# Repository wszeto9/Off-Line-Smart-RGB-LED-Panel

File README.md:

# Off-Line Smart RGB LED Panel
A constant current driver made to to drive 100W RGB COB LEDs straight from mains power

[Interactive BOM](https://htmlpreview.github.io/?https://github.com/wszeto9/Off-Line-Smart-RGBCCT-LED-Panel/blob/main/ibom.html)

## Testing and Validation

This is probably the most complicated board I've made so far! This isn't because it has more circuits or anything, but rather because it's powered off AC mains. I can't just plug it in and hope that it works. There's an insignificant chance it doesn't, and who knows what will happen to the circuit if a component doesn't work as expected. It goes without saying, don't try this at home! It's taken me years to feel okay designing a system like this, and it isn't a project to build on a whim. Nevertheless, let's look into the bringup process. 

### 24VDC Buck

One of the easiest things to test is the 24V Buck converter. Solder it up, and stick +50VDC (0.1A max) between +HV and -HV. It's safe enough for me to feel comfortable testing it alone. Flip the power switch, and the conviniently placed LED indicator turns on, suggesting that the power rail works. Sticking a multimeter on the power rail shows... ***25.5V***? Interesting. I wonder if it's because there's no load on it. I'll have to look at it again once I get some load put together. For now, it's fine. The 3.3V regulator doesn't care as long as it's below 28V, and the LED drivers are okay with up to a few hundred volts. The LNK3206 IC the design is based on also has a soft-start feature, and that seems to work great. Rise time seems to be ~ 16 ms, no overshoots or anything. Cool! 

*Soft-start of 24V rail. +HV = 60V DC*

### Bulk Capacitor Discharge Testing

Before I even consider plugging this into the wall, I need to ensure that the bulk capacitors are able to drain in a reasonable time after being unplugged. Bulk capacitors without bleed resistors are one of the scariest things to see. There's no telling whether it's at 400V or 0V simply by looking, and one slip up during measurement would be very dangerous. In this test, I'll inject +60VDC between +HV and -HV. Then I'll measure the voltage across C2. +60VDC is high enough that I can extrapolate discharge rate to +169VDC, while also being low enough that I'd be okay starting with it. 

*Schematic of Bleed Circuit, Rev A02*

*Voltage across C2 after +HV is turned off. Initial discharge rate seems to be approximately 20V/100ms, or 200V/s*

Looking at the discharge rate, it seems to be much higher than expected. The calculations show a 15 second time-constant from a 1M/15.5uF system. The measured time constant is much less than 1 second. This might be since the Buck converter is attached to the circuit, which has ~ 10k of load at 24V. Assuming 100% efficiency, that would equate to ~ 24k of load at 60V, and it's also a psudo-constant power load since the buck converter wants to keep the output at 24V. With a 24k / 15.5uF system, that gets a tau of 0.36 seconds, fairly close to what's observed. The constant power load also explain why the discharge rate seems to accelerate when the capacitor voltage gets closer to 25V.

### LED Current Regulation Testing, 62VDC

Once the +24V Buck was validated, the LED driver can be validated next. +HV is set to +62VDC since that's the highest 2x 30V power supplies can deliver. A 12V LED strip was used to be a load for testing. The LED strip drew 1A at 12V for a total of 12W of power draw. The power supplies were set to 0.2A max in order to ensure that in the event that the LED driver did not work, the LEDs would not be supplied past their rated power. 

When powered up, the LEDs do not turn on until a 3.3V PWM signal was applied. Once the PWM signal was applied, the LED strip did not shine at full brightness. This is likely because the LD configuration only allows for full power draw when +HV is at 169VDC. Since +HV is +62VDC, the LEDs are likely at roughly 1/3 the maximum current draw. 

Scope capture of LED current regulation, Rev A02. +HV = 62V, PWM = 20% Duty Cycle, 3.3V logic. Blue = PWM, Green = GATE, Yellow = Isense. 0.1V on Isense is 0.33A.

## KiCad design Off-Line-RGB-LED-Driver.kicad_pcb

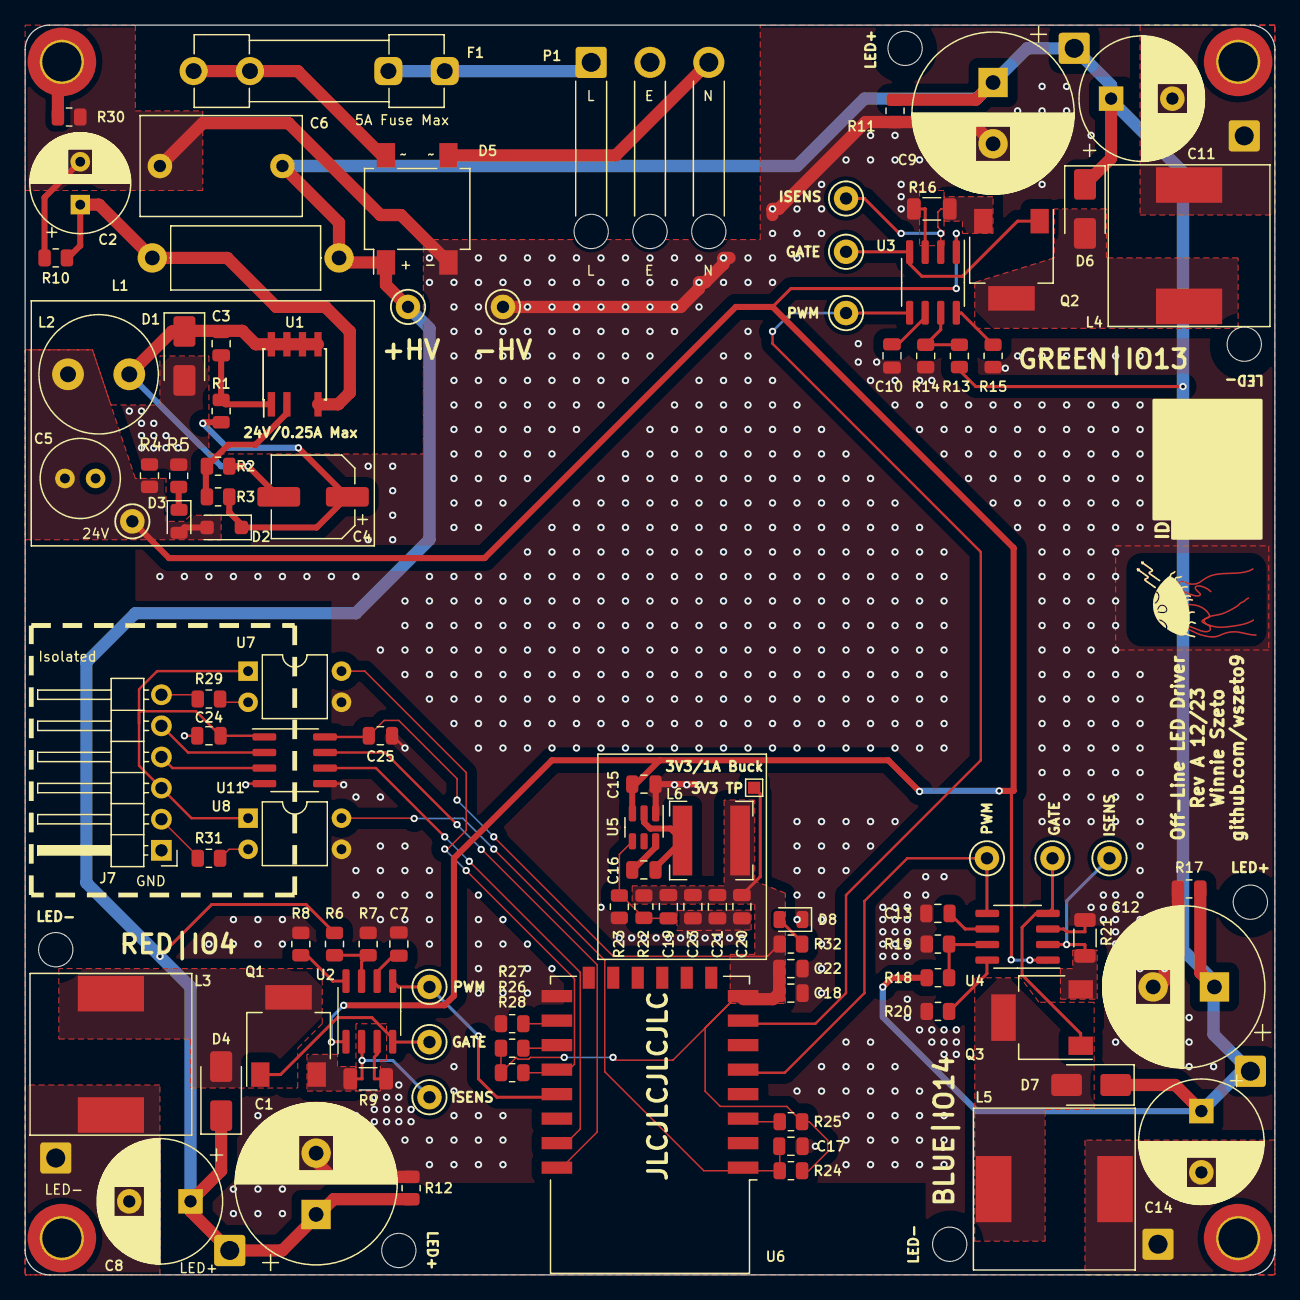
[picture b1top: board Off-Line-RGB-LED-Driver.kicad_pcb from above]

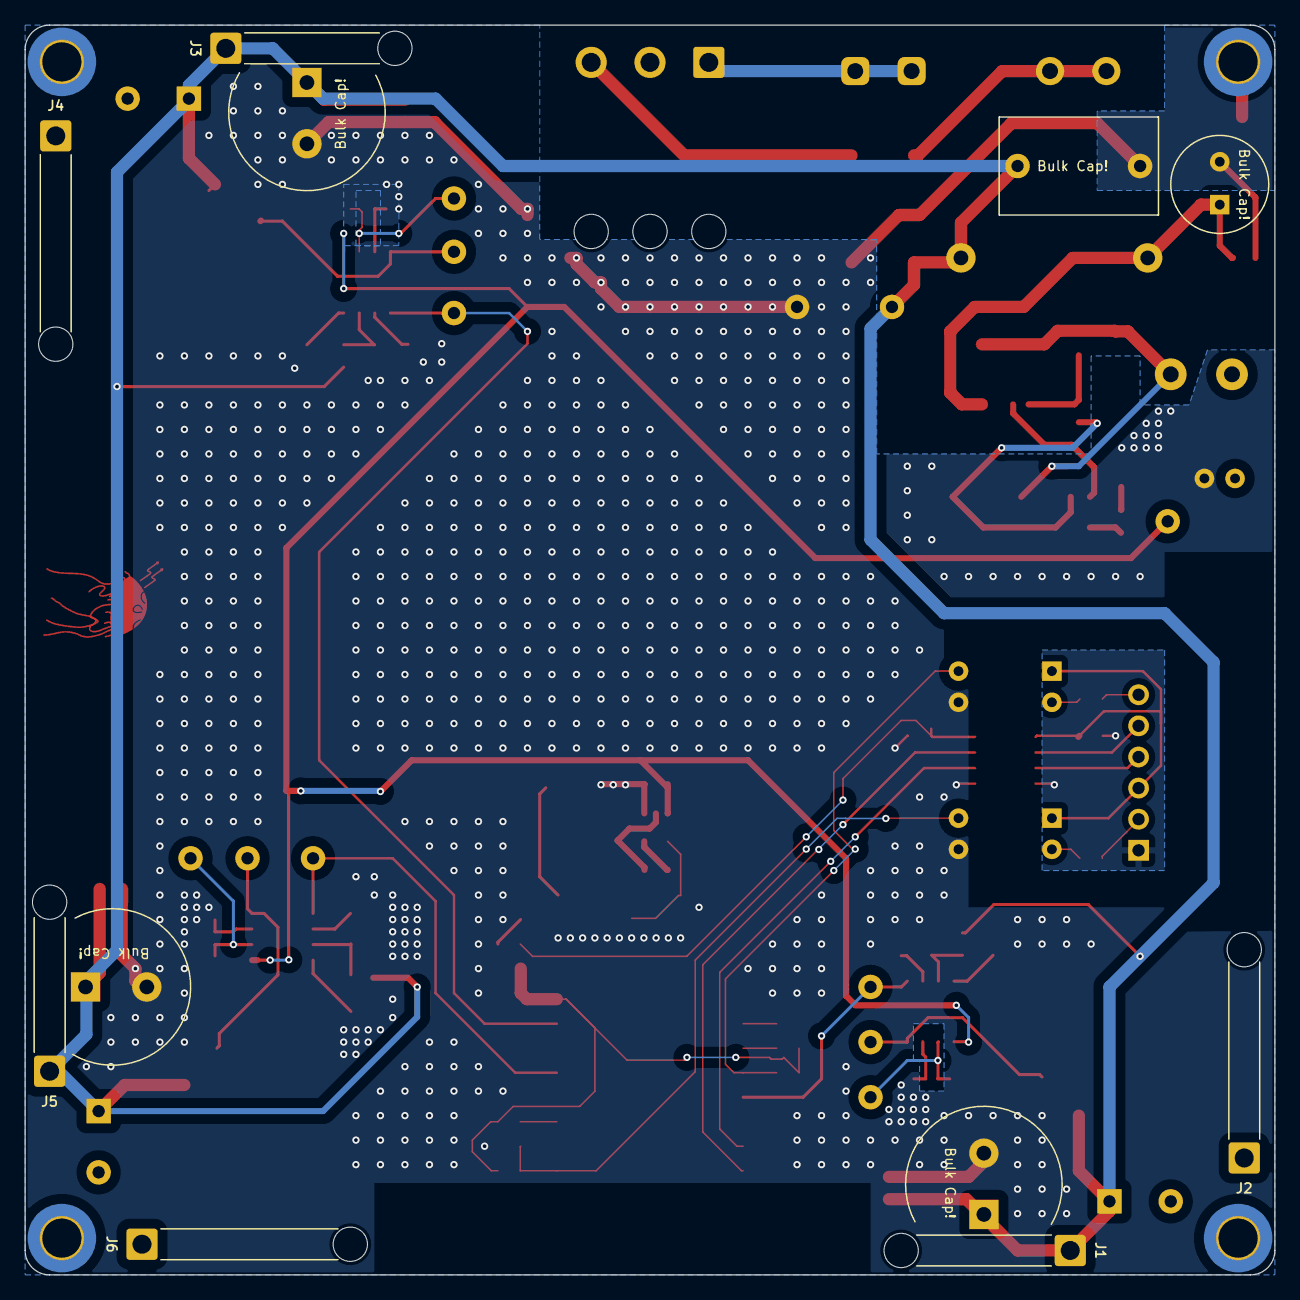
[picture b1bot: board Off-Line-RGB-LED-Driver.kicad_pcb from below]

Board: 2 copper layers, 102.0 x 102.0 mm, 110 parts (6 on the bottom side), 57 nets.

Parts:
C1, C9, C12: 56uF/450V; CP_Radial_D13.0mm_P5.00mm
C2: 15uF/400V; CP_Radial_D8.0mm_P3.50mm
C3, C16, C24, C25: 0805,100nF,50V,X7R; C_0805_2012Metric
C4: 10uF/35V; CP_Elec_6.3x5.4
C5: 100uF/35V; C_Radial_D6.3mm_H11.0mm_P2.50mm
C6: 150nF/630V; C_Rect_L13.0mm_W8.0mm_P10.00mm_FKS3_FKP3_MKS4
C7, C10, C13, C17, C18: 0805,1uF,50V,X7R; C_0805_2012Metric
C8, C11, C14: 220uF/50V; CP_Radial_D10.0mm_P5.00mm
C15: 0805,10uF,50V,X5R; C_0805_2012Metric
C19: 0805,47pF,50V,C0G; C_0805_2012Metric
C20, C21, C23: 0805,47uF,6.3V,X5R; C_0805_2012Metric
C22: 0805,10nF,50V,X7R; C_0805_2012Metric
D1, D4, D6, D7: ES2G; D_SMA
D2: RS1MWF-7; D_SOD-123F
D3, D8: LED 0805 W; LED_0805_2012Metric
D5: DB207S; Diode_Bridge_Vishay_DFSFlat
F1: 5A/250V; Fuseholder_Clip-5x20mm_Littelfuse_100_Inline_P20.50x4.60mm_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
H1, H2, H3, H4: MountingHole_Pad; MountingHole_3.2mm_M3_DIN965_Pad_TopBottom
J1, J3, J5: SolderWire_LED+; SolderWire-0.75sqmm_1x01_D1.25mm_OD2.3mm_Relief
J2, J4, J6: SolderWire_LED-; SolderWire-0.75sqmm_1x01_D1.25mm_OD2.3mm_Relief_longer
J7: Conn_01x06_Pin; PinHeader_1x06_P2.54mm_Horizontal
L1: 820uH/0.29A; L_Axial_L12.0mm_D5.0mm_P15.24mm_Horizontal_Fastron_MISC
L2: 1mH/0.3A; L_Radial_D9.5mm_P5.00mm_Fastron_07HVP
L3, L4, L5: 470uH/1.5A; L_Neosid_SM-NE127
L6: 33uH/1.5A; L_Bourns-SRN6028
LOGO##1: Logo
P1: Conn_WallPlug_Earth; SolderWire-0.75sqmm_1x03_P4.8mm_D1.25mm_OD2.3mm_Relief
Q1, Q2, Q3: IPN70R1K4P7S; SOT-223-3_TabPin2
R1: 0805,36k; R_0805_2012Metric
R2: 0805,2k; R_0805_2012Metric
R3, R23: 0805,22k; R_0805_2012Metric
R4, R24, R25, R26, R27, R28: 0805,10k; R_0805_2012Metric
R5, R6, R11, R12, R13, R17, R18: 0805,510k; R_0805_2012Metric
R7, R14, R19: 0805,750; R_0805_2012Metric
R8, R15, R20: 0805,75k; R_0805_2012Metric
R9, R16, R21: 1206,0.3; R_1206_3216Metric
R10, R30: 0805,1M; R_0805_2012Metric
R22: 0805,100k; R_0805_2012Metric
R29, R31: 0805,330; R_0805_2012Metric
R32: 0805,1k; R_0805_2012Metric
TP1: 5000 (Red); TestPoint_Keystone_5000-5004_Miniature
TP2, TP6, TP9: 5003 (Orange); TestPoint_Keystone_5000-5004_Miniature
TP3, TP7, TP10: 5119 (Purple); TestPoint_Keystone_5000-5004_Miniature
TP4, TP5, TP8: 5117 (Blue); TestPoint_Keystone_5000-5004_Miniature
TP11: 5001 (Black); TestPoint_Keystone_5000-5004_Miniature
TP12: 5002 (White); TestPoint_Keystone_5000-5004_Miniature
TP13: TestPoint_Pad_1.0x1.0mm
U1: LNK3206D; PowerIntegrations_SO-8C
U2, U3, U4: AL9910-5S-13; SOIC-8_3.9x4.9mm_P1.27mm
U5: TPS54202DDC; SOT-23-6
U6: ESP-12F; ESP-12E
U7, U8: PC817; DIP-4_W7.62mm
U11: ISO7321C; SOIC-8_3.9x4.9mm_P1.27mm

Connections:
+3.3V: C18.1, C19.1, C20.1, C21.1, C22.1, C23.1, C25.2, L6.2, R22.1, R24.1, R25.1, R26.1, R28.1, R32.1, TP13.1, U6.8 (VCC), U11.8 (VCC2)
+5VA: C24.2, J7.3, U7.1, U8.1, U11.1 (VCC1)
+24V: C5.1, C15.1, D2.2 (A), D3.2 (A), L2.2, R4.1, TP1.1, U2.1 (VIN), U3.1 (VIN), U4.1 (VIN), U5.3 (VIN)
/AC_L: F1.1, P1.1 (AC_P)
/AC_L_Fused: D5.4, F1.2
/AC_N: D5.3, P1.3 (AC_N)
/AC_Rectified_+: C1.1, C6.1, C8.1, C9.1, C11.1, C12.1, C14.1, D4.1 (K), D5.1 (+), D6.1 (K), D7.1 (K), J1.1, J3.1, J5.1, L1.1, R6.1, R11.1, R12.1, R13.1, R17.1, R18.1, TP11.1
/BSig: TP8.1, U4.5 (PWM_D), U6.5 (GPIO14)
/ESP8266/DTR: J7.6, R29.1
/ESP8266/GPIO0: R28.2, U6.18 (GPIO0), U7.4
/ESP8266/RST: C17.1, R24.2, U6.1 (~RST), U8.4
/ESP8266/RTS: J7.2, R31.1
/ESP8266/RXD0: U6.21 (GPIO3/RXD), U11.6 (OUTB)
/ESP8266/RXD_ESP: J7.4, U11.3 (INB)
/ESP8266/TXD0: U6.22 (GPIO1/TXD), U11.7 (INA)
/ESP8266/TXD_ESP: J7.5, U11.2 (OUTA)
/GSig: TP5.1, U3.5 (PWM_D), U6.7 (GPIO13)
/Non-Isolated-24V-Switcher/AC_FILT: C2.1, L1.2, R10.1, U1.4 (D)
/Non-Isolated-24V-Switcher/FB: R2.1, R3.1, U1.2 (FB)
/Non-Isolated-24V-Switcher/SwitchNode: C3.2, C4.2, D1.1 (K), L2.1, R2.2, U1.5 (S), U1.6 (S), U1.7 (S), U1.8 (S)
/PFCLEDBuck1/LD: R13.2, R14.1, U3.7 (LD)
/PFCLEDBuck1/LED-: C11.2, J4.1, L4.2
/PFCLEDBuck1/LED_SW_NODE: D6.2 (A), L4.1, Q2.2 (D)
/PFCLEDBuck2/LD: R18.2, R19.1, U4.7 (LD)
/PFCLEDBuck2/LED-: C14.2, J6.1, L5.2
/PFCLEDBuck2/LED_SW_NODE: D7.2 (A), L5.1, Q3.2 (D)
/PFCLEDBuck/LD: R6.2, R7.1, U2.7 (LD)
/PFCLEDBuck/LED-: C8.2, J2.1, L3.2
/PFCLEDBuck/LED_SW_NODE: D4.2 (A), L3.1, Q1.2 (D)
/RSig: TP4.1, U2.5 (PWM_D), U6.19 (GPIO4)
GND: C1.2, C2.2, C5.2, C6.2, C7.1, C9.2, C10.1, C12.2, C13.1, C15.2, C17.2, C18.2, C20.2, C21.2, C22.2, C23.2, C25.1, D1.2 (A), D5.2 (-), D8.1 (K), R4.2, R5.2, R7.2, R8.2, R9.2, R10.2, R11.2, R12.2, R14.2, R15.2, R16.2, R17.2, R19.2, R20.2, R21.2, R23.2, R27.2, R30.2, TP12.1, U2.3 (GND), U3.3 (GND), U4.3 (GND), U5.1 (GND), U6.15 (GND), U7.3, U8.3, U11.5 (GND2)
GNDS: C24.1, J7.1, U11.4 (GND1)
unnamed: C4.1, D2.1 (K), R1.2, R3.2
unnamed: D3.1 (K), R5.1
unnamed: D8.2 (A), R32.2
unnamed: H1.1, R30.1
unnamed: Q1.1 (G), TP2.1, U2.4 (GATE)
unnamed: Q1.3 (S), R9.1, TP3.1, U2.2 (CS)
unnamed: Q2.1 (G), TP6.1, U3.4 (GATE)
unnamed: Q2.3 (S), R16.1, TP7.1, U3.2 (CS)
unnamed: Q3.1 (G), TP9.1, U4.4 (GATE)
unnamed: Q3.3 (S), R21.1, TP10.1, U4.2 (CS)
unnamed: R29.2, U7.2
unnamed: R31.2, U8.2
unnamed: C3.1, R1.1, U1.1 (BP/M)
unnamed: R8.1, U2.8 (ROSC)
unnamed: C7.2, U2.6 (VDD)
unnamed: R15.1, U3.8 (ROSC)
unnamed: C10.2, U3.6 (VDD)
unnamed: R20.1, U4.8 (ROSC)
unnamed: C13.2, U4.6 (VDD)
unnamed: C16.1, U5.6 (BOOT)
unnamed: C19.2, R22.2, R23.1, U5.4 (FB)
unnamed: C16.2, L6.1, U5.2 (SW)
unnamed: R25.2, U6.3 (EN)
unnamed: R26.2, U6.17 (GPIO2)
unnamed: R27.1, U6.16 (GPIO15)

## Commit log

2023-12-25 Laid out Rev A
2023-12-31 [A02] Edited R4, R5
    R4 20k -> 10k since nothing else uses 20k
    R5 10k -> 510k to reduce D3 LED brightness
2023-12-31 Added documentation for 24V buck validation
2023-12-31 accidentily made thermal reliefs, reverting them
2024-01-28 added current regulation test
